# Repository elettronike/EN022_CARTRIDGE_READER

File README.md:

# EN022 CARTRIDGE READER

## Supported Console Cartridge.

## (GB) Game Boy
[Game Boy related schematics](https://github.com/Gekkio/gb-schematics?tab=readme-ov-file) 

[Jeff Frohwein's GameBoy Tech Page](http://www.devrs.com/gb/files/hardware.html)
Cartridge Voltage 3.3V
System Clock: 4MHz

## (GBA) Gameboy Advanced

[retrosix](https://www.retrosix.wiki/schematics-game-boy-advance) Here are the original scanned schematics of the Game Boy Advance console.

## (NES)

[schematics](https://github.com/schenkzoola/NES)
[nesdev cartridge connector](https://www.nesdev.org/wiki/Cartridge_connector)

Cartridge Voltage 3.3V

## (SNES)

### SNES CIC

## (N64) Nintendo 64

## (MS) Master System

## PCE/TG16	

## Wonderswan	

## CASIO  Loopy

## References

# License

All the schematics in this repository are licensed very liberally under CC BY 4.0, so you can copy, distribute, modify, or even sell them commercially if you want. There's just one requirement: attribution

Basically it just means this: don't remove the original creator's name, or at least somehow acknowledge them. [Here's the full description about it in CC BY 4.0(https://creativecommons.org/licenses/by/4.0/#deed-conditions)]

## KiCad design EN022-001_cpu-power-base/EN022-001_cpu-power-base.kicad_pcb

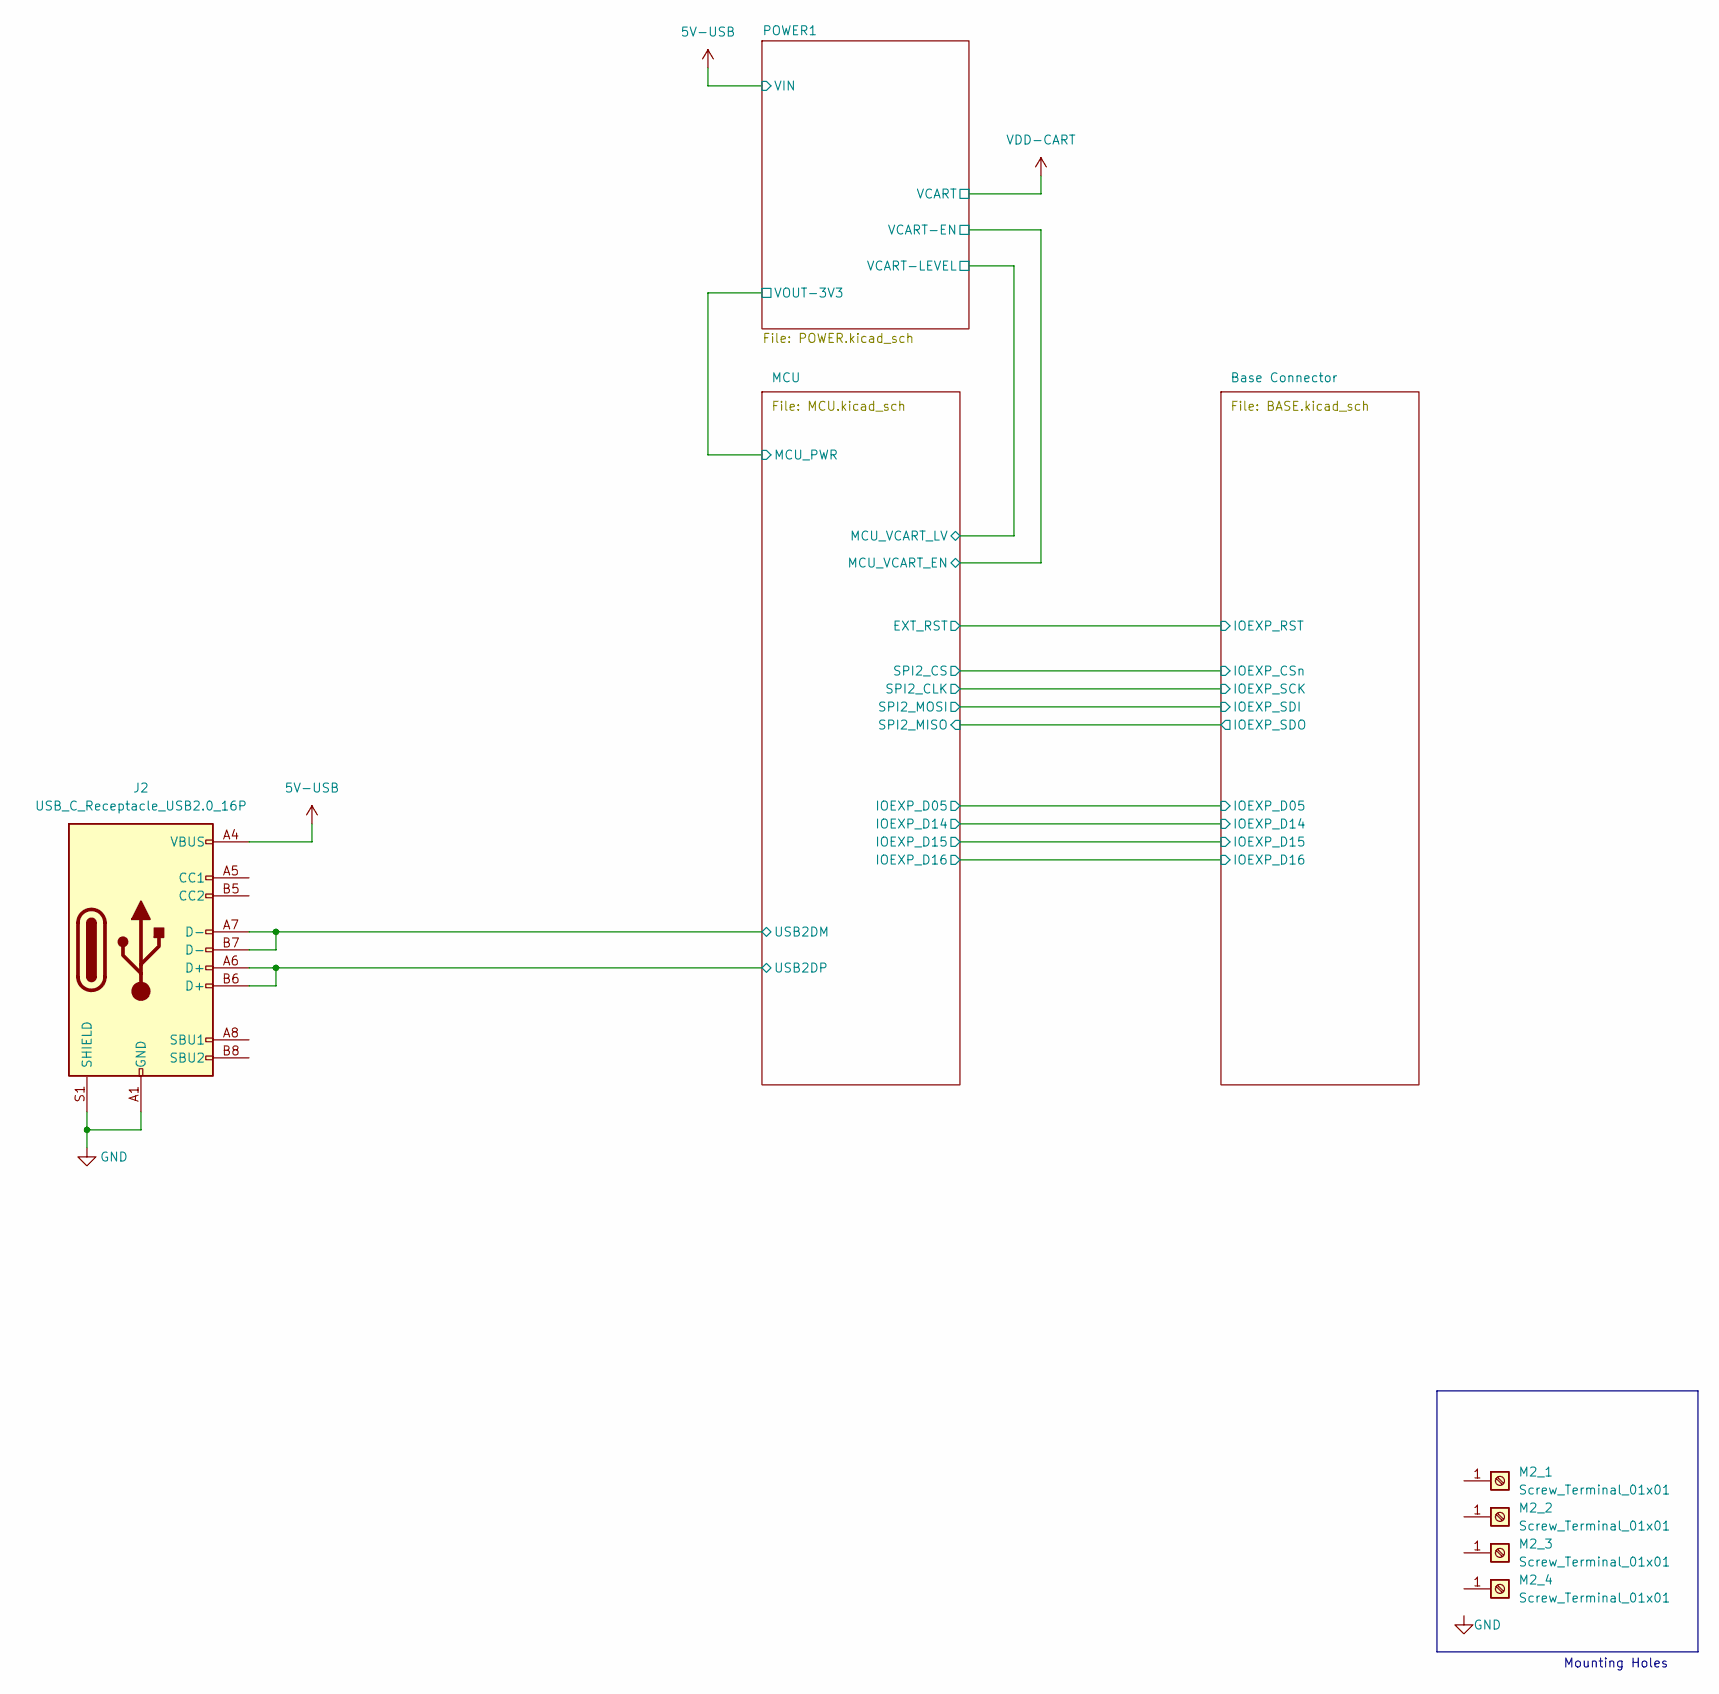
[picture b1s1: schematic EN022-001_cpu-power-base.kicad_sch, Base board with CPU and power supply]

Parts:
J2: USB_C_Receptacle_USB2.0_16P; USB_C_Receptacle_GCT_USB4105-xx-A_16P_TopMnt_Horizontal
M2_1, M2_2, M2_3, M2_4: Screw_Terminal_01x01

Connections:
5V-USB: J2.A4 (VBUS), J2.A9 (VBUS), J2.B4 (VBUS), J2.B9 (VBUS); also elsewhere on the board
/MCU/USB2DM: J2.A7 (D-), J2.B7 (D-); also elsewhere on the board
/MCU/USB2DP: J2.A6 (D+), J2.B6 (D+); also elsewhere on the board
GND: J2.A1 (GND), J2.A12 (GND), J2.B1 (GND), J2.B12 (GND), J2.S1 (SHIELD); also elsewhere on the board

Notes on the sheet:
Mounting Holes

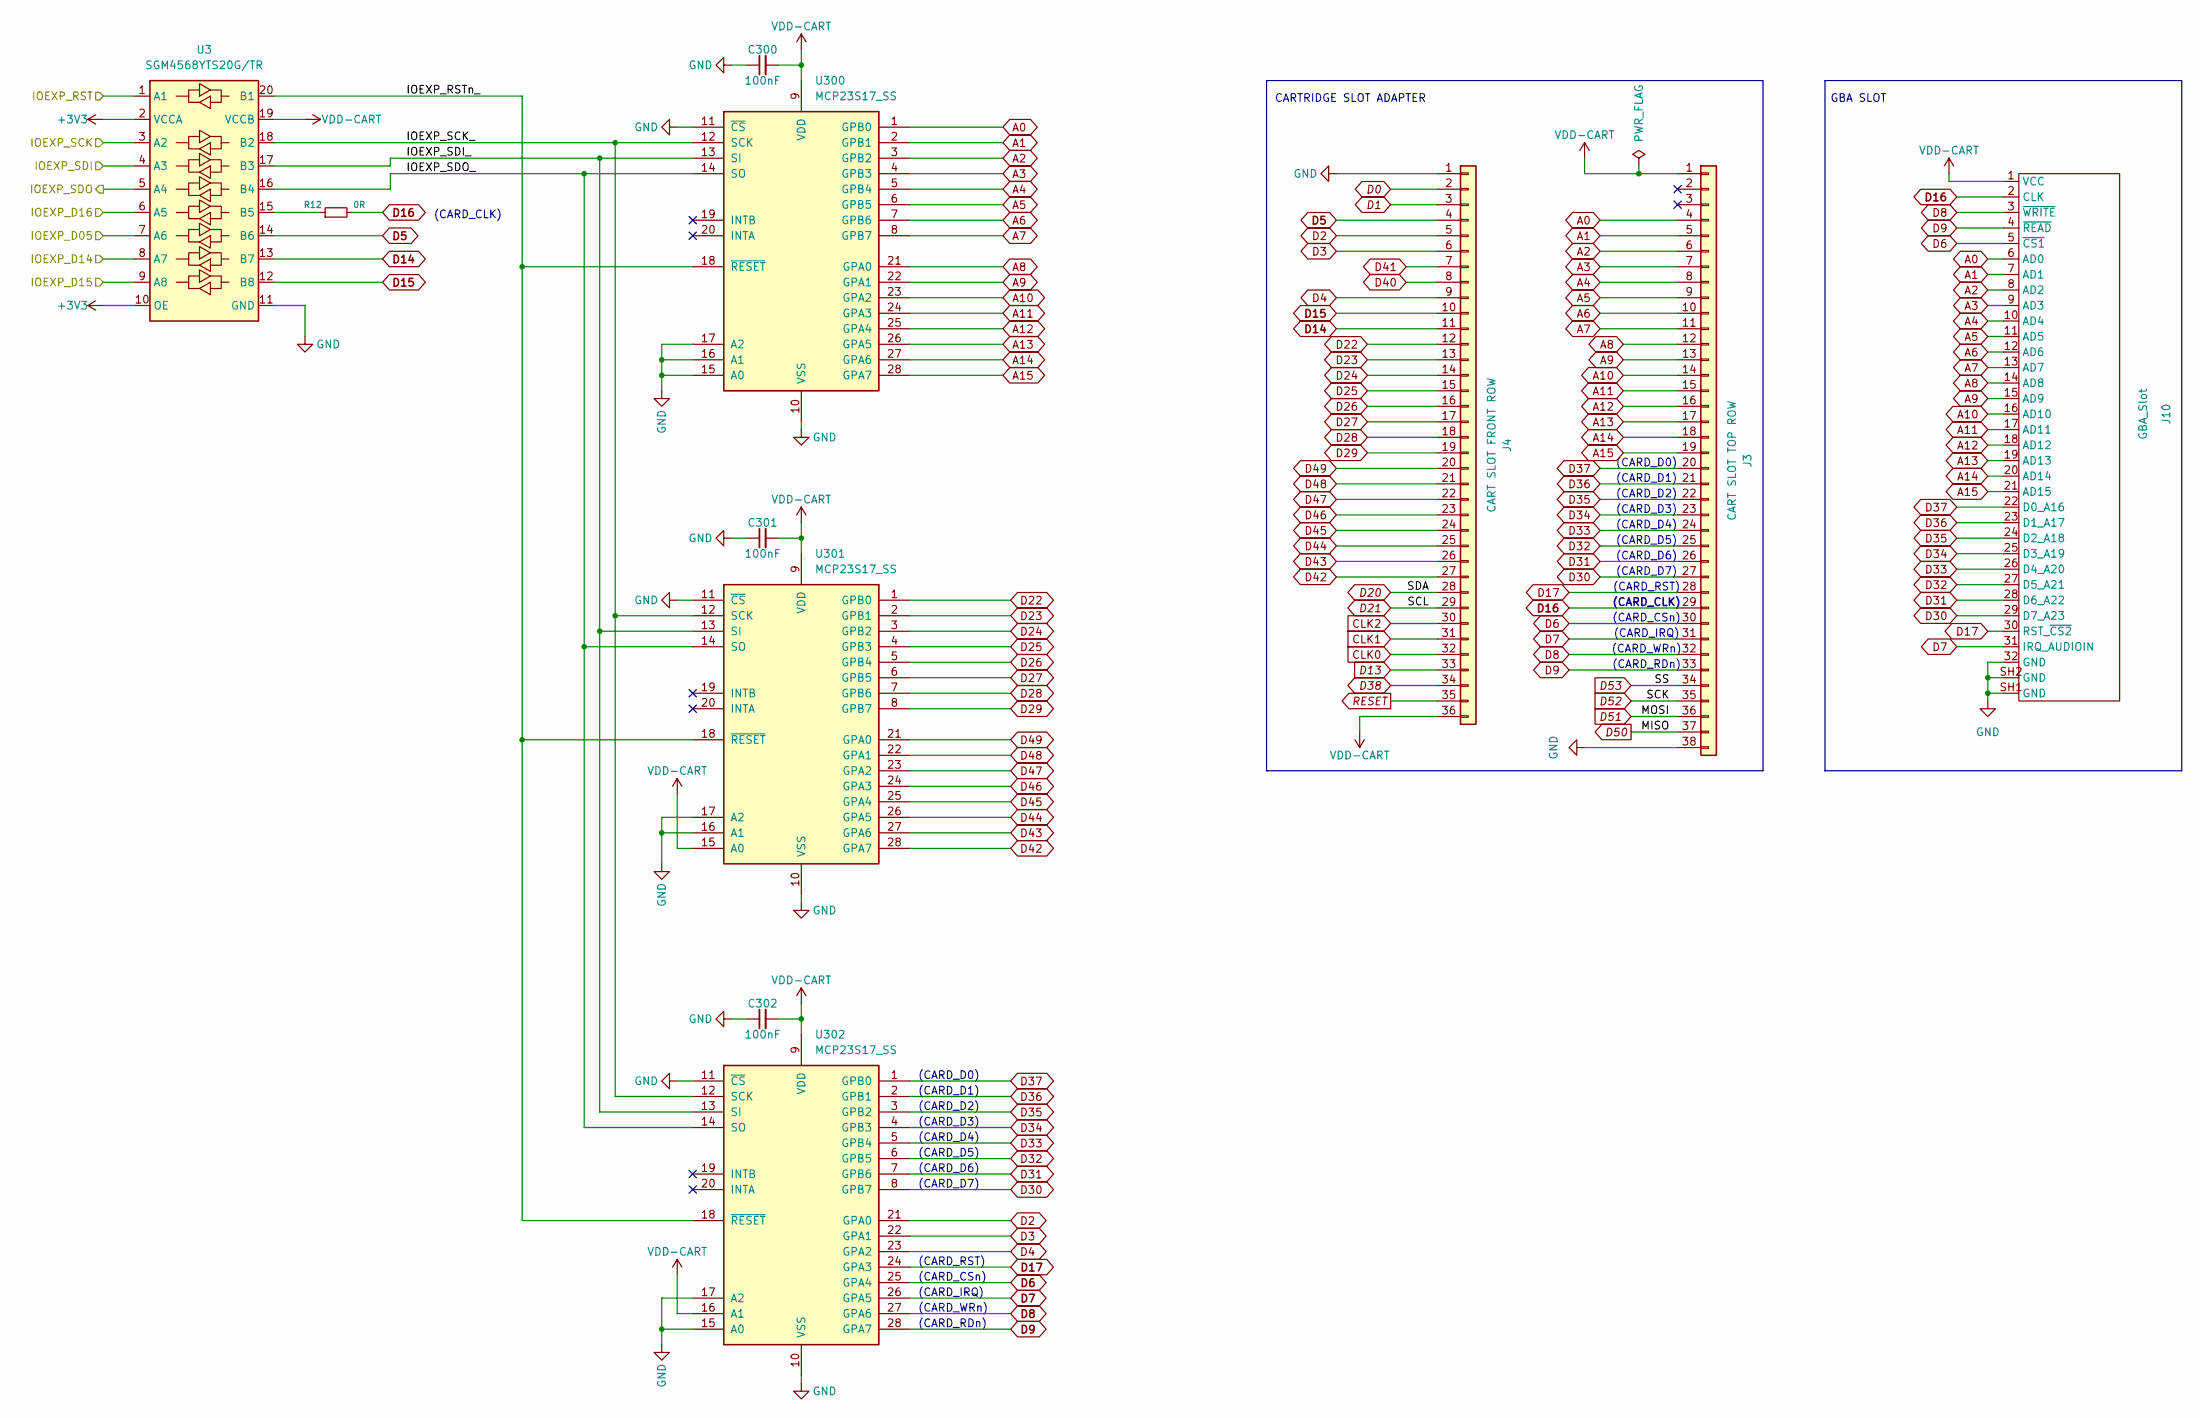
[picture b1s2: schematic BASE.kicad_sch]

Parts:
C300, C301, C302: 100nF; C_0805_2012Metric_Pad1.18x1.45mm_HandSolder
J3: CART SLOT TOP ROW; Cartridge_Port_Adapter-Back
J4: CART SLOT FRONT ROW; Cartridge_Port_Adapter-Front
J10: GBA_Slot
R12: 0R; R_0805_2012Metric_Pad1.20x1.40mm_HandSolder
U3: SGM4568YTS20G/TR; TSSOP-20_4.4x6.5mm_P0.65mm
U300, U301, U302: MCP23S17_SS; SSOP-28_5.3x10.2mm_P0.65mm

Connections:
+3V3: U3.2 (VCCA), U3.10 (OE); also elsewhere on the board
/Base Connector/IOEXP_D05: U3.7 (A6); also elsewhere on the board
/Base Connector/IOEXP_D14: U3.8 (A7); also elsewhere on the board
/Base Connector/IOEXP_D15: U3.9 (A8); also elsewhere on the board
/Base Connector/IOEXP_D16: U3.6 (A5); also elsewhere on the board
/Base Connector/IOEXP_RST: U3.1 (A1); also elsewhere on the board
/Base Connector/IOEXP_RSTn_: U3.20 (B1), U300.18 (~RESET), U301.18 (~RESET), U302.18 (~RESET)
/Base Connector/IOEXP_SCK: U3.3 (A2); also elsewhere on the board
/Base Connector/IOEXP_SCK_: U3.18 (B2), U300.12 (SCK), U301.12 (SCK), U302.12 (SCK)
/Base Connector/IOEXP_SDI: U3.4 (A3); also elsewhere on the board
/Base Connector/IOEXP_SDI_: U3.17 (B3), U300.13 (SI), U301.13 (SI), U302.13 (SI)
/Base Connector/IOEXP_SDO: U3.5 (A4); also elsewhere on the board
/Base Connector/IOEXP_SDO_: U3.16 (B4), U300.14 (SO), U301.14 (SO), U302.14 (SO)
A0: J3.4, J10.6 (AD0), U300.1 (GPB0)
A1: J3.5, J10.7 (AD1), U300.2 (GPB1)
A2: J3.6, J10.8 (AD2), U300.3 (GPB2)
A3: J3.7, J10.9 (AD3), U300.4 (GPB3)
A4: J3.8, J10.10 (AD4), U300.5 (GPB4)
A5: J3.9, J10.11 (AD5), U300.6 (GPB5)
A6: J3.10, J10.12 (AD6), U300.7 (GPB6)
A7: J3.11, J10.13 (AD7), U300.8 (GPB7)
A8: J3.12, J10.14 (AD8), U300.21 (GPA0)
A9: J3.13, J10.15 (AD9), U300.22 (GPA1)
A10: J3.14, J10.16 (AD10), U300.23 (GPA2)
A11: J3.15, J10.17 (AD11), U300.24 (GPA3)
A12: J3.16, J10.18 (AD12), U300.25 (GPA4)
A13: J3.17, J10.19 (AD13), U300.26 (GPA5)
A14: J3.18, J10.20 (AD14), U300.27 (GPA6)
A15: J3.19, J10.21 (AD15), U300.28 (GPA7)
CLK0: J4.32
CLK1: J4.31
CLK2: J4.30
D0: J4.2
D1: J4.3
D2: J4.5, U302.21 (GPA0)
D3: J4.6, U302.22 (GPA1)
D4: J4.9, U302.23 (GPA2)
D5: J4.4, U3.14 (B6)
D6: J3.30, J10.5 (~CS1), U302.25 (GPA4)
D7: J3.31, J10.31 (IRQ_AUDIOIN), U302.26 (GPA5)
D8: J3.32, J10.3 (~WRITE), U302.27 (GPA6)
D9: J3.33, J10.4 (~READ), U302.28 (GPA7)
D13: J4.33
D14: J4.11, U3.13 (B7)
D15: J4.10, U3.12 (B8)
D16: J3.29, J10.2 (CLK), R12.2
D17: J3.28, J10.30 (RST_~CS2), U302.24 (GPA3)
D20: J4.28
D21: J4.29
D22: J4.12, U301.1 (GPB0)
D23: J4.13, U301.2 (GPB1)
D24: J4.14, U301.3 (GPB2)
D25: J4.15, U301.4 (GPB3)
D26: J4.16, U301.5 (GPB4)
D27: J4.17, U301.6 (GPB5)
D28: J4.18, U301.7 (GPB6)
D29: J4.19, U301.8 (GPB7)
D30: J3.27, J10.29 (D7_A23), U302.8 (GPB7)
D31: J3.26, J10.28 (D6_A22), U302.7 (GPB6)
D32: J3.25, J10.27 (D5_A21), U302.6 (GPB5)
D33: J3.24, J10.26 (D4_A20), U302.5 (GPB4)
D34: J3.23, J10.25 (D3_A19), U302.4 (GPB3)
D35: J3.22, J10.24 (D2_A18), U302.3 (GPB2)
D36: J3.21, J10.23 (D1_A17), U302.2 (GPB1)
D37: J3.20, J10.22 (D0_A16), U302.1 (GPB0)
D38: J4.34
D40: J4.8
D41: J4.7
D42: J4.27, U301.28 (GPA7)
D43: J4.26, U301.27 (GPA6)
D44: J4.25, U301.26 (GPA5)
D45: J4.24, U301.25 (GPA4)
D46: J4.23, U301.24 (GPA3)
D47: J4.22, U301.23 (GPA2)
D48: J4.21, U301.22 (GPA1)
D49: J4.20, U301.21 (GPA0)
D50: J3.37
D51: J3.36
D52: J3.35
D53: J3.34
GND: C300.1, C301.1, C302.1, J3.38, J4.1, J10.32 (GND), J10.SH1 (GND), J10.SH2 (GND), U3.11 (GND), U300.10 (VSS), U300.11 (~CS), U300.15 (A0), U300.16 (A1), U300.17 (A2), U301.10 (VSS), U301.11 (~CS), U301.16 (A1), U301.17 (A2), U302.10 (VSS), U302.11 (~CS), U302.15 (A0), U302.17 (A2); also elsewhere on the board
unnamed: R12.1, U3.15 (B5)
RESET: J4.35
VDD-CART: C300.2, C301.2, C302.2, J3.1, J4.36, J10.1 (VCC), U3.19 (VCCB), U300.9 (VDD), U301.9 (VDD), U301.15 (A0), U302.9 (VDD), U302.16 (A1); also elsewhere on the board

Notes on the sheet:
(CARD_D7)
(CARD_D0)
(CARD_CLK)
(CARD_D6)
GBA SLOT
(CARD_D5)
(CARD_D3)
(CARD_WRn)
(CARD_CSn)
(CARD_D1)
CARTRIDGE SLOT ADAPTER
(CARD_D2)
(CARD_IRQ)
(CARD_D4)
(CARD_RDn)
(CARD_RST)

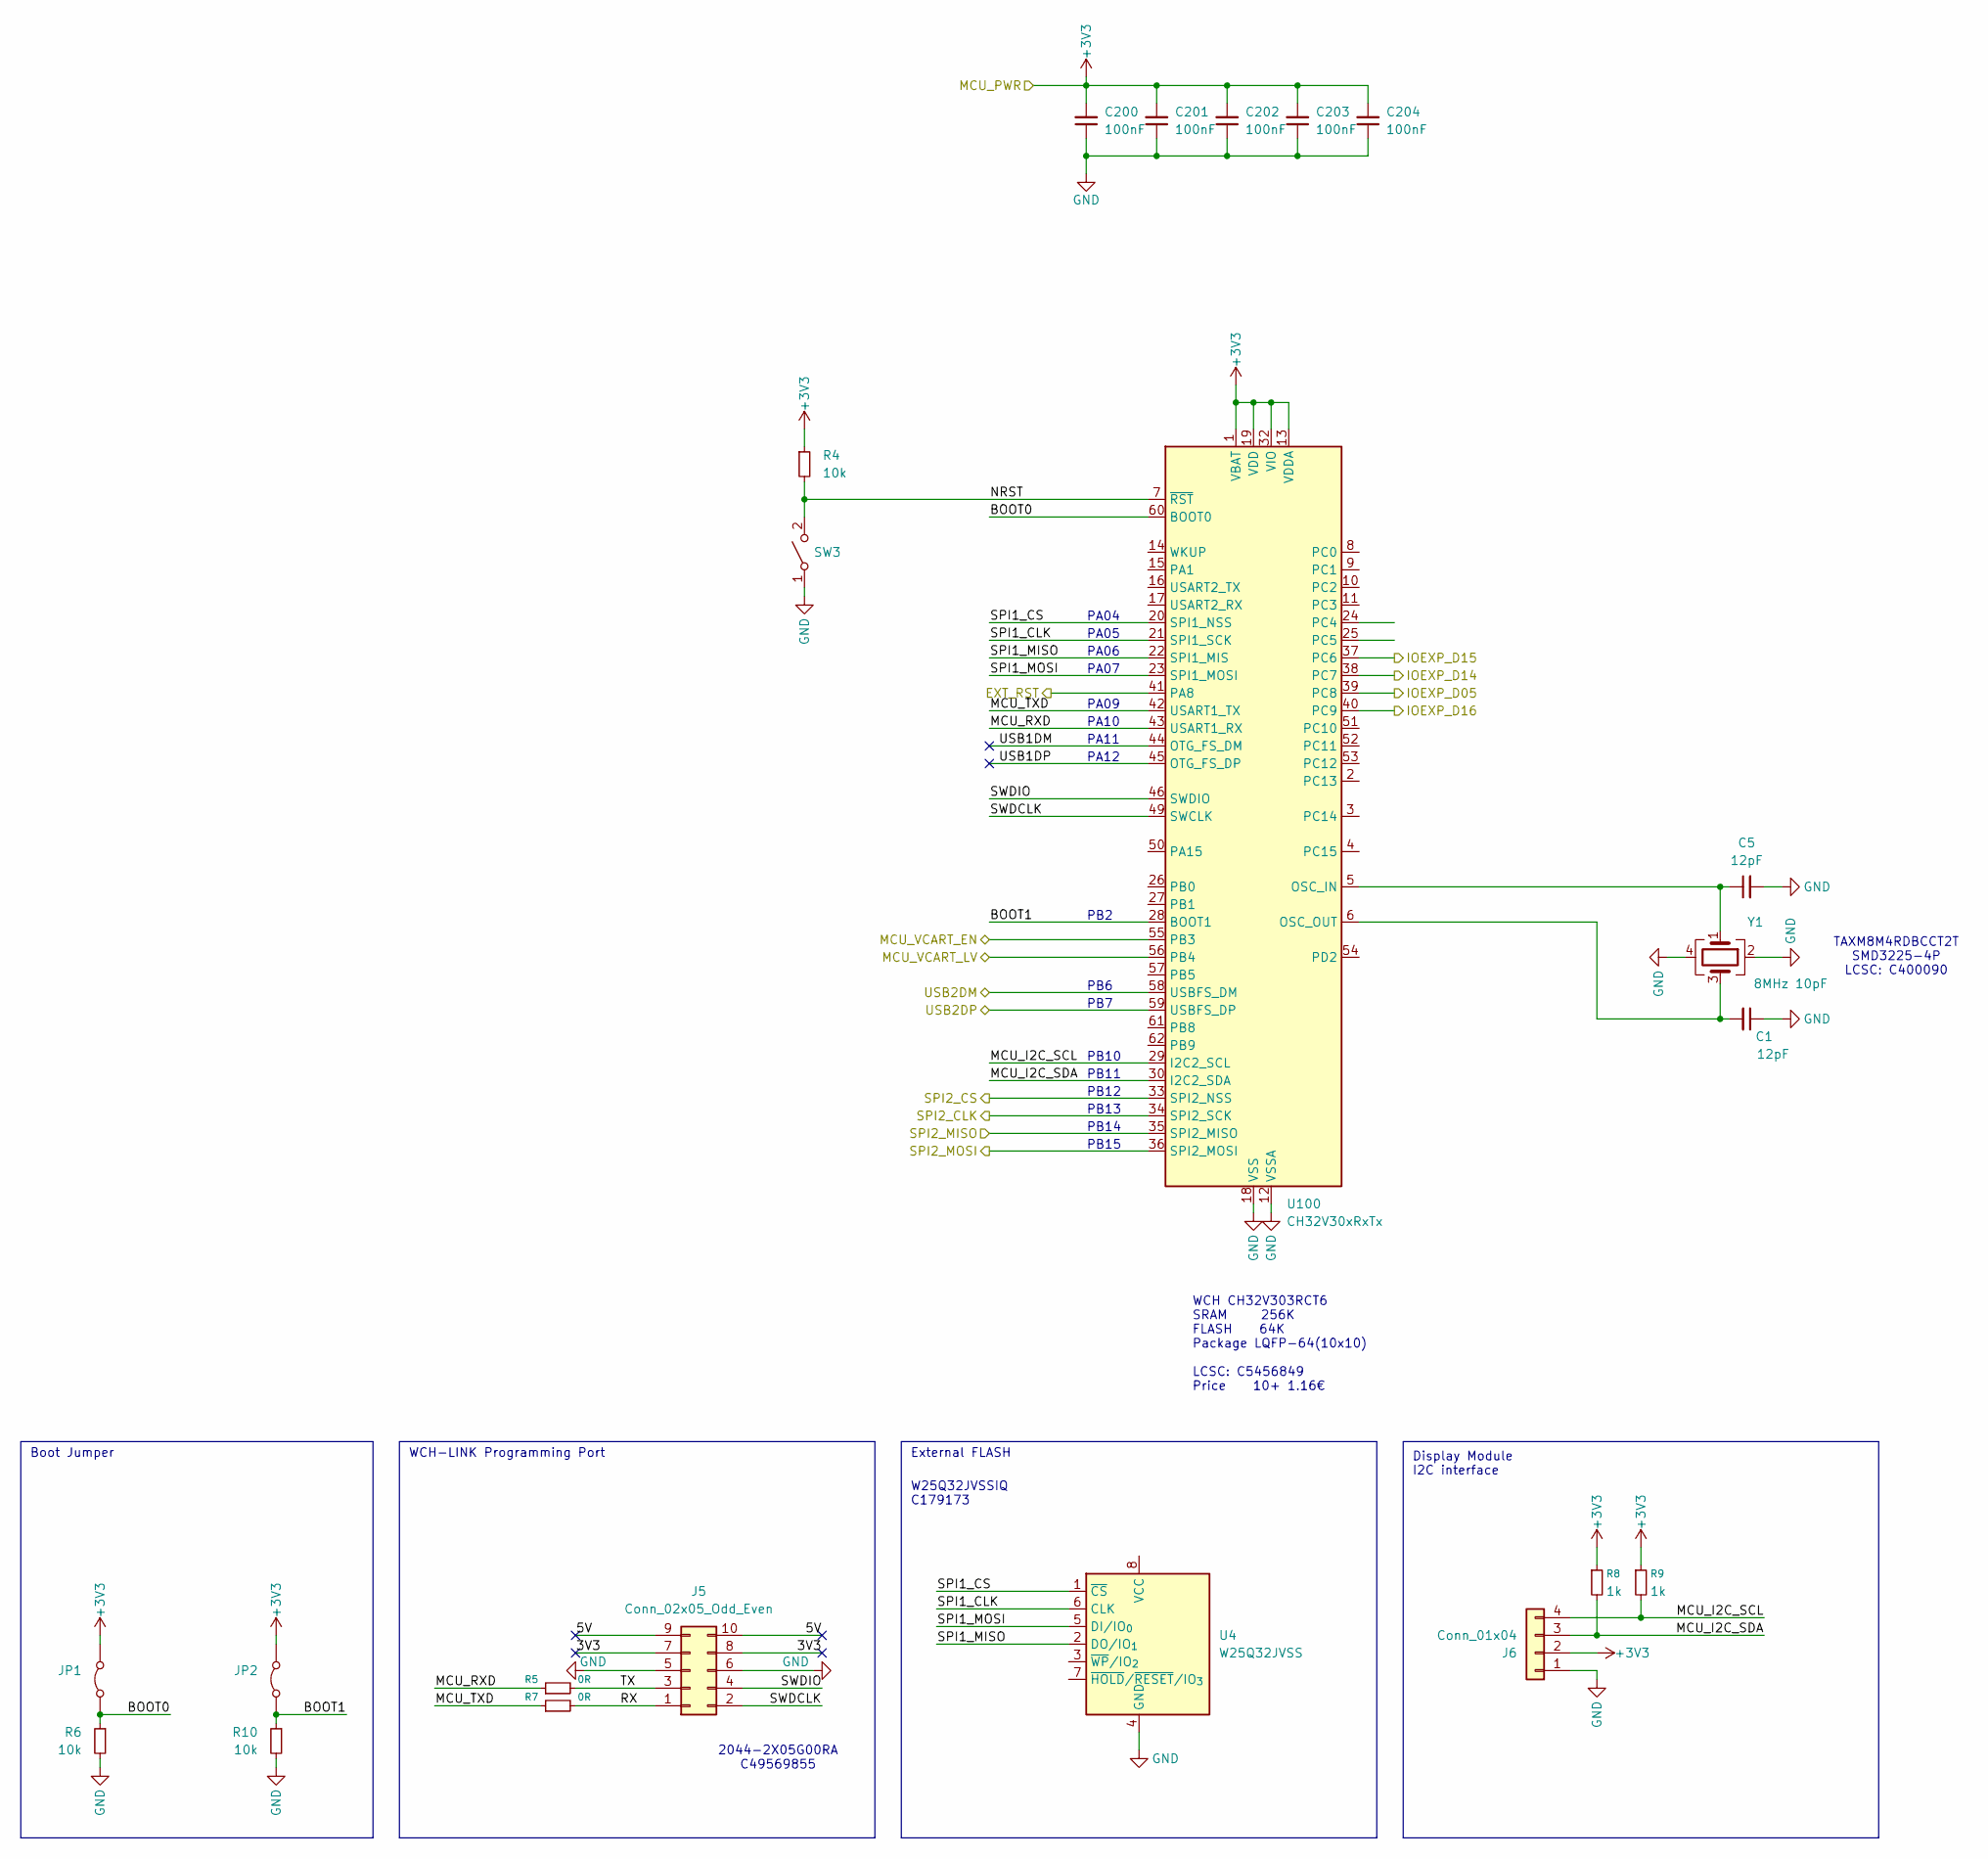
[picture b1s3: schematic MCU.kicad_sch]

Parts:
C1, C5: 12pF; C_0603_1608Metric_Pad1.08x0.95mm_HandSolder
C200, C201, C202, C203, C204: 100nF; C_0805_2012Metric_Pad1.18x1.45mm_HandSolder
J5: Conn_02x05_Odd_Even; PinSocket_2x05_P2.54mm_Horizontal
J6: Conn_01x04; PinHeader_1x04_P2.54mm_Vertical
JP1, JP2: Jumper_2_Bridged; PinHeader_1x02_P2.54mm_Vertical
R4, R6, R10: 10k; R_0805_2012Metric_Pad1.20x1.40mm_HandSolder
R5, R7: 0R; R_0805_2012Metric_Pad1.20x1.40mm_HandSolder
R8, R9: 1k; R_0805_2012Metric_Pad1.20x1.40mm_HandSolder
SW3: TC-6615-7-260G; SW_Tactile_SPST_Angled_PTS645Vx58-2LFS
U4: W25Q32JVSS; SOIC-8_5.3x5.3mm_P1.27mm
U100: CH32V30xRxTx; LQFP-64_10x10mm_P0.5mm
Y1: 8MHz 10pF; Crystal_SMD_3225-4Pin_3.2x2.5mm_HandSoldering

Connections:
+3V3: C200.2, C201.2, C202.2, C203.2, C204.2, J6.2, JP1.1 (A), JP2.1 (A), R4.1, R8.1, R9.1, U100.1 (VBAT), U100.13 (VDDA), U100.19 (VDD), U100.32 (VIO), U100.48 (VDD), U100.64 (VIO); also elsewhere on the board
/Base Connector/IOEXP_D05: U100.39 (PC8); also elsewhere on the board
/Base Connector/IOEXP_D14: U100.38 (PC7); also elsewhere on the board
/Base Connector/IOEXP_D15: U100.37 (PC6); also elsewhere on the board
/Base Connector/IOEXP_D16: U100.40 (PC9); also elsewhere on the board
/Base Connector/IOEXP_RST: U100.41 (PA8); also elsewhere on the board
/Base Connector/IOEXP_SCK: U100.34 (SPI2_SCK); also elsewhere on the board
/Base Connector/IOEXP_SDI: U100.36 (SPI2_MOSI); also elsewhere on the board
/Base Connector/IOEXP_SDO: U100.35 (SPI2_MISO); also elsewhere on the board
/MCU/3V3: J5.7, J5.8
/MCU/5V: J5.9, J5.10
/MCU/BOOT0: JP1.2 (B), R6.1, U100.60 (BOOT0)
/MCU/BOOT1: JP2.2 (B), R10.1, U100.28 (BOOT1)
/MCU/MCU_I2C_SCL: J6.4, R9.2, U100.29 (I2C2_SCL)
/MCU/MCU_I2C_SDA: J6.3, R8.2, U100.30 (I2C2_SDA)
/MCU/MCU_RXD: R5.1, U100.43 (USART1_RX)
/MCU/MCU_TXD: R7.1, U100.42 (USART1_TX)
/MCU/MCU_VCART_EN: U100.55 (PB3); also elsewhere on the board
/MCU/MCU_VCART_LV: U100.56 (PB4); also elsewhere on the board
/MCU/NRST: R4.2, SW3.2 (B), U100.7 (~RST)
/MCU/RX: J5.1, R7.2
/MCU/SPI1_CLK: U4.6 (CLK), U100.21 (SPI1_SCK)
/MCU/SPI1_CS: U4.1 (~CS), U100.20 (SPI1_NSS)
/MCU/SPI1_MISO: U4.2 (DO/IO_{1}), U100.22 (SPI1_MIS)
/MCU/SPI1_MOSI: U4.5 (DI/IO_{0}), U100.23 (SPI1_MOSI)
/MCU/SPI2_CS: U100.33 (SPI2_NSS)
/MCU/SWDCLK: J5.2, U100.49 (SWCLK)
/MCU/SWDIO: J5.4, U100.46 (SWDIO)
/MCU/TX: J5.3, R5.2
/MCU/USB1DM: U100.44 (OTG_FS_DM)
/MCU/USB1DP: U100.45 (OTG_FS_DP)
/MCU/USB2DM: U100.58 (USBFS_DM); also elsewhere on the board
/MCU/USB2DP: U100.59 (USBFS_DP); also elsewhere on the board
GND: C1.1, C5.2, C200.1, C201.1, C202.1, C203.1, C204.1, J5.5, J5.6, J6.1, R6.2, R10.2, SW3.1 (A), U4.4 (GND), U100.12 (VSSA), U100.18 (VSS), U100.31 (VSS), U100.47 (VSS), U100.63 (VSS), Y1.2, Y1.4; also elsewhere on the board
unnamed: C5.1, U100.5 (OSC_IN), Y1.1
unnamed: C1.2, U100.6 (OSC_OUT), Y1.3

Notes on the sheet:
WCH-LINK Programming Port
PB7
WCH CH32V303RCT6 SRAM 256K FLASH 64K Package LQFP-64(10x10) LCSC: C5456849 Price 10+ 1.16€
W25Q32JVSSIQ C179173
PB11
PB15
TAXM8M4RDBCCT2T SMD3225-4P LCSC: C400090
PB2
PB13
PB14
PB12
PB10
External FLASH
Display Module I2C interface
PA10
PB6
PA04
PA11
PA05
Boot Jumper
PA09
PA06
2044-2X05G00RA C49569855
PA12
PA07

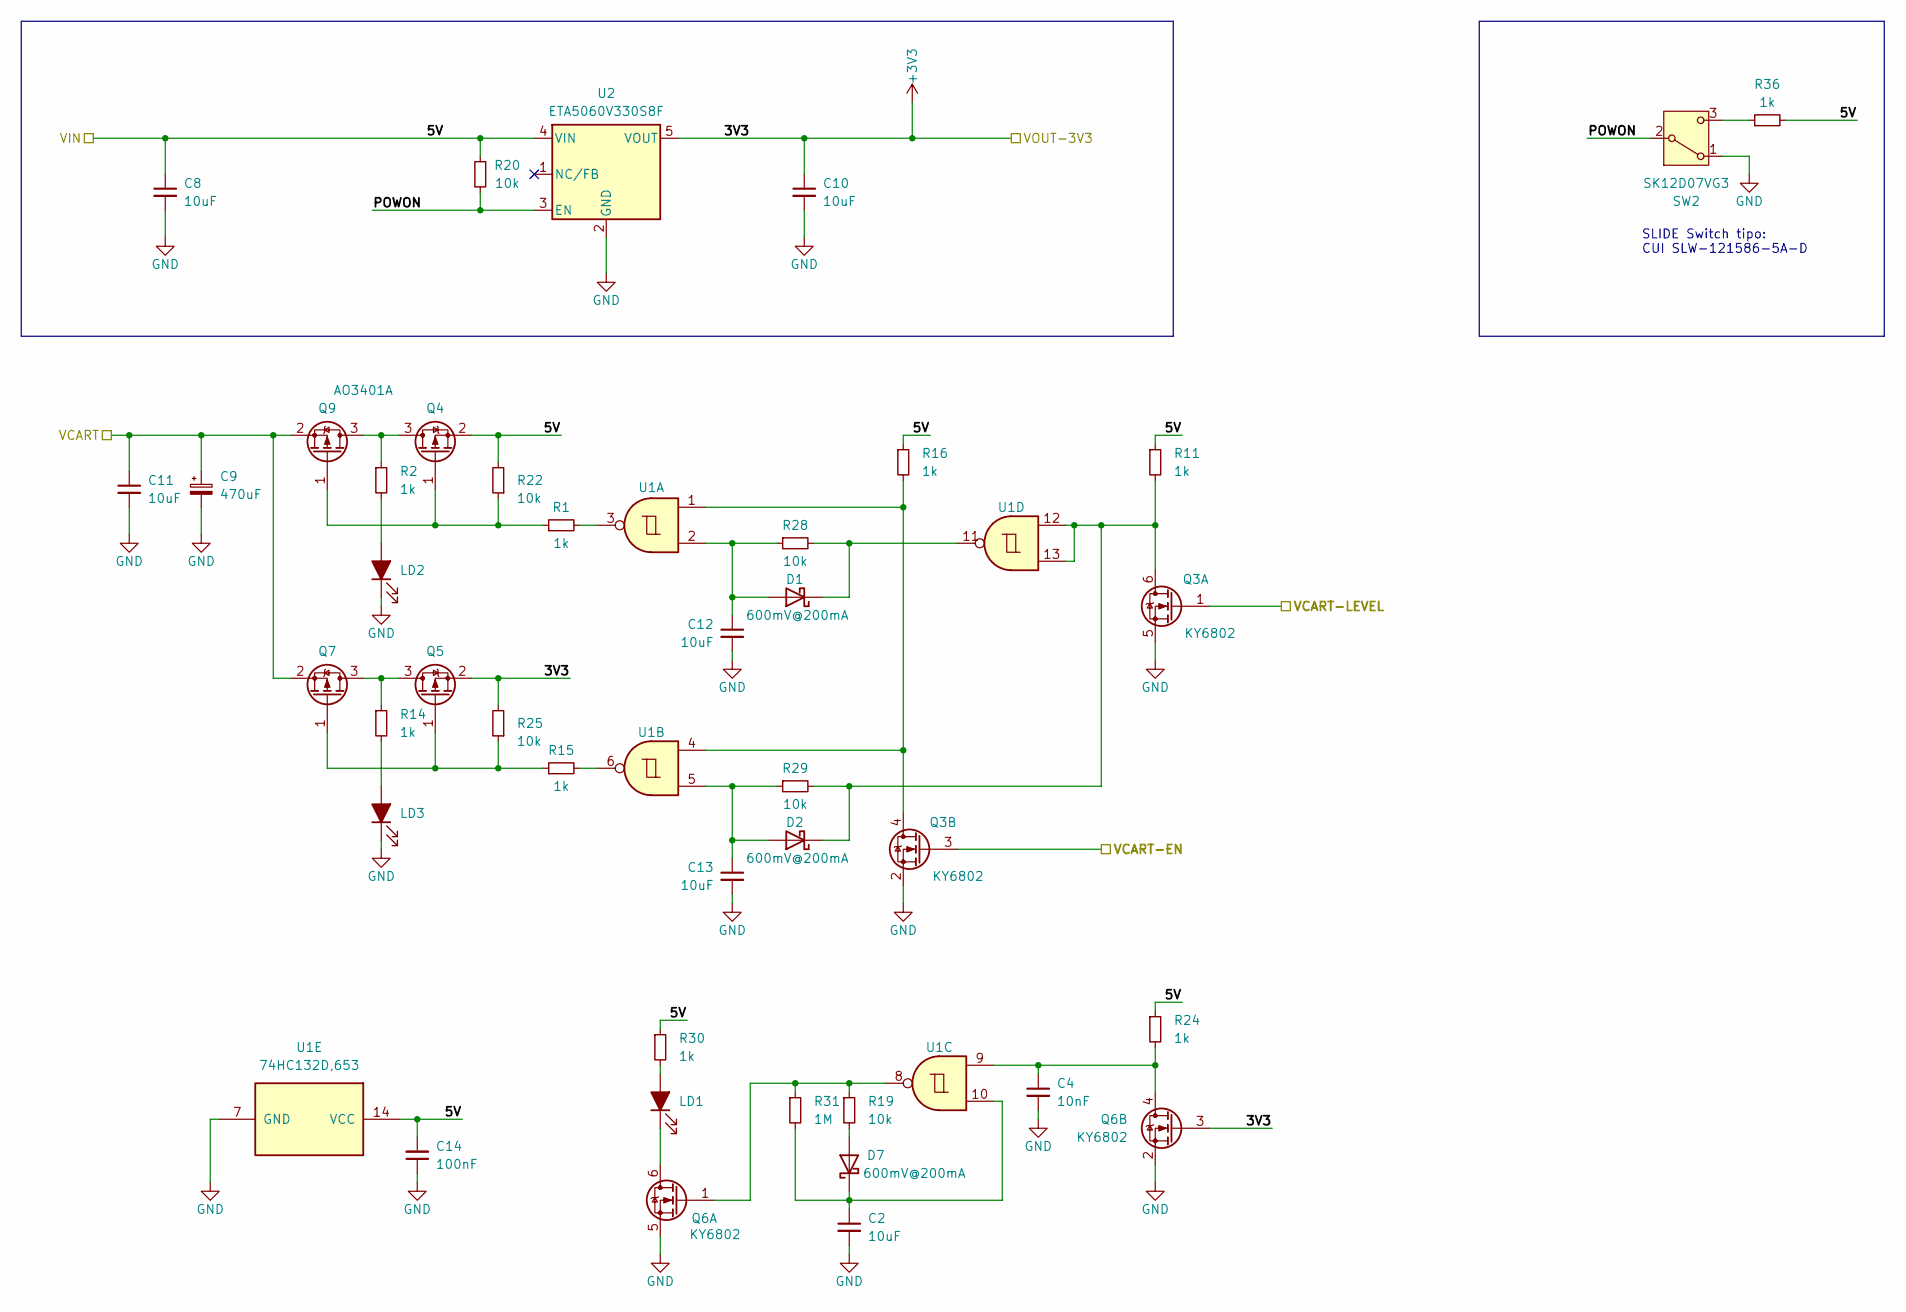
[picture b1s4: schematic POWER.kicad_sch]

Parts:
C2, C8, C10, C11, C12, C13: 10uF; C_1206_3216Metric_Pad1.33x1.80mm_HandSolder
C4: 10nF; C_0805_2012Metric_Pad1.18x1.45mm_HandSolder
C9: 470uF; CP_Elec_6.3x7.7
C14: 100nF; C_0805_2012Metric_Pad1.18x1.45mm_HandSolder
D1, D2, D7: 600mV@200mA; D_SOD-123F
LD1, LD2, LD3: LED_Filled; LED_0805_2012Metric_Pad1.15x1.40mm_HandSolder
Q3, Q6: KY6802; SOT-23-6_Handsoldering
Q4, Q5, Q7, Q9: AO3401; SOT-23
R1, R2, R11, R14, R15, R16, R24, R30, R36: 1k; R_0805_2012Metric_Pad1.20x1.40mm_HandSolder
R19, R20, R22, R25, R28, R29: 10k; R_0805_2012Metric_Pad1.20x1.40mm_HandSolder
R31: 1M; R_0805_2012Metric_Pad1.20x1.40mm_HandSolder
SW2: SK12D07VG3; SW_Slide_SPDT_Angled_CK_OS102011MA1Q
U1: 74HC132D,653; SOIC-14_3.9x8.7mm_P1.27mm
U2: ETA5060V330S8F; SOT-89-5

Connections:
5V-USB: C8.1, C14.2, Q4.2 (S), R11.1, R16.1, R20.1, R22.2, R24.1, R30.1, R36.2, U1.14 (VCC), U2.4 (VIN); also elsewhere on the board
+3V3: C10.1, Q5.2 (S), Q6.3 (G), R25.2, U2.5 (VOUT); also elsewhere on the board
/MCU/MCU_VCART_EN: Q3.3 (G); also elsewhere on the board
/MCU/MCU_VCART_LV: Q3.1 (G); also elsewhere on the board
/POWER1/POWON: R20.2, SW2.2 (B), U2.3 (EN)
GND: C2.2, C4.2, C8.2, C9.2, C10.2, C11.2, C12.2, C13.2, C14.1, LD2.1 (K), LD3.1 (K), Q3.2 (S), Q3.5 (S), Q6.2 (S), Q6.5 (S), SW2.1 (A), U1.7 (GND), U2.2 (GND); also elsewhere on the board
unnamed: C12.1, D1.2 (A), R28.1, U1.2
unnamed: D1.1 (K), R28.2, U1.11
unnamed: C13.1, D2.2 (A), R29.1, U1.5
unnamed: D2.1 (K), Q3.6 (D), R11.2, R29.2, U1.12, U1.13
unnamed: D7.2 (A), R19.2
unnamed: C2.1, D7.1 (K), R31.2, U1.10
unnamed: LD1.2 (A), R30.2
unnamed: LD1.1 (K), Q6.6 (D)
unnamed: LD2.2 (A), R2.2
unnamed: LD3.2 (A), R14.2
unnamed: Q3.4 (D), R16.2, U1.1, U1.4
unnamed: Q4.3 (D), Q9.3 (D), R2.1
unnamed: Q4.1 (G), Q9.1 (G), R1.1, R22.1
unnamed: Q5.3 (D), Q7.3 (D), R14.1
unnamed: Q5.1 (G), Q7.1 (G), R15.1, R25.1
unnamed: Q6.1 (G), R19.1, R31.1, U1.8
unnamed: C4.1, Q6.4 (D), R24.2, U1.9
unnamed: R1.2, U1.3
unnamed: R15.2, U1.6
unnamed: R36.1, SW2.3 (C)
VDD-CART: C9.1, C11.1, Q7.2 (S), Q9.2 (S); also elsewhere on the board

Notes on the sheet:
SLIDE Switch tipo: CUI SLW-121586-5A-D

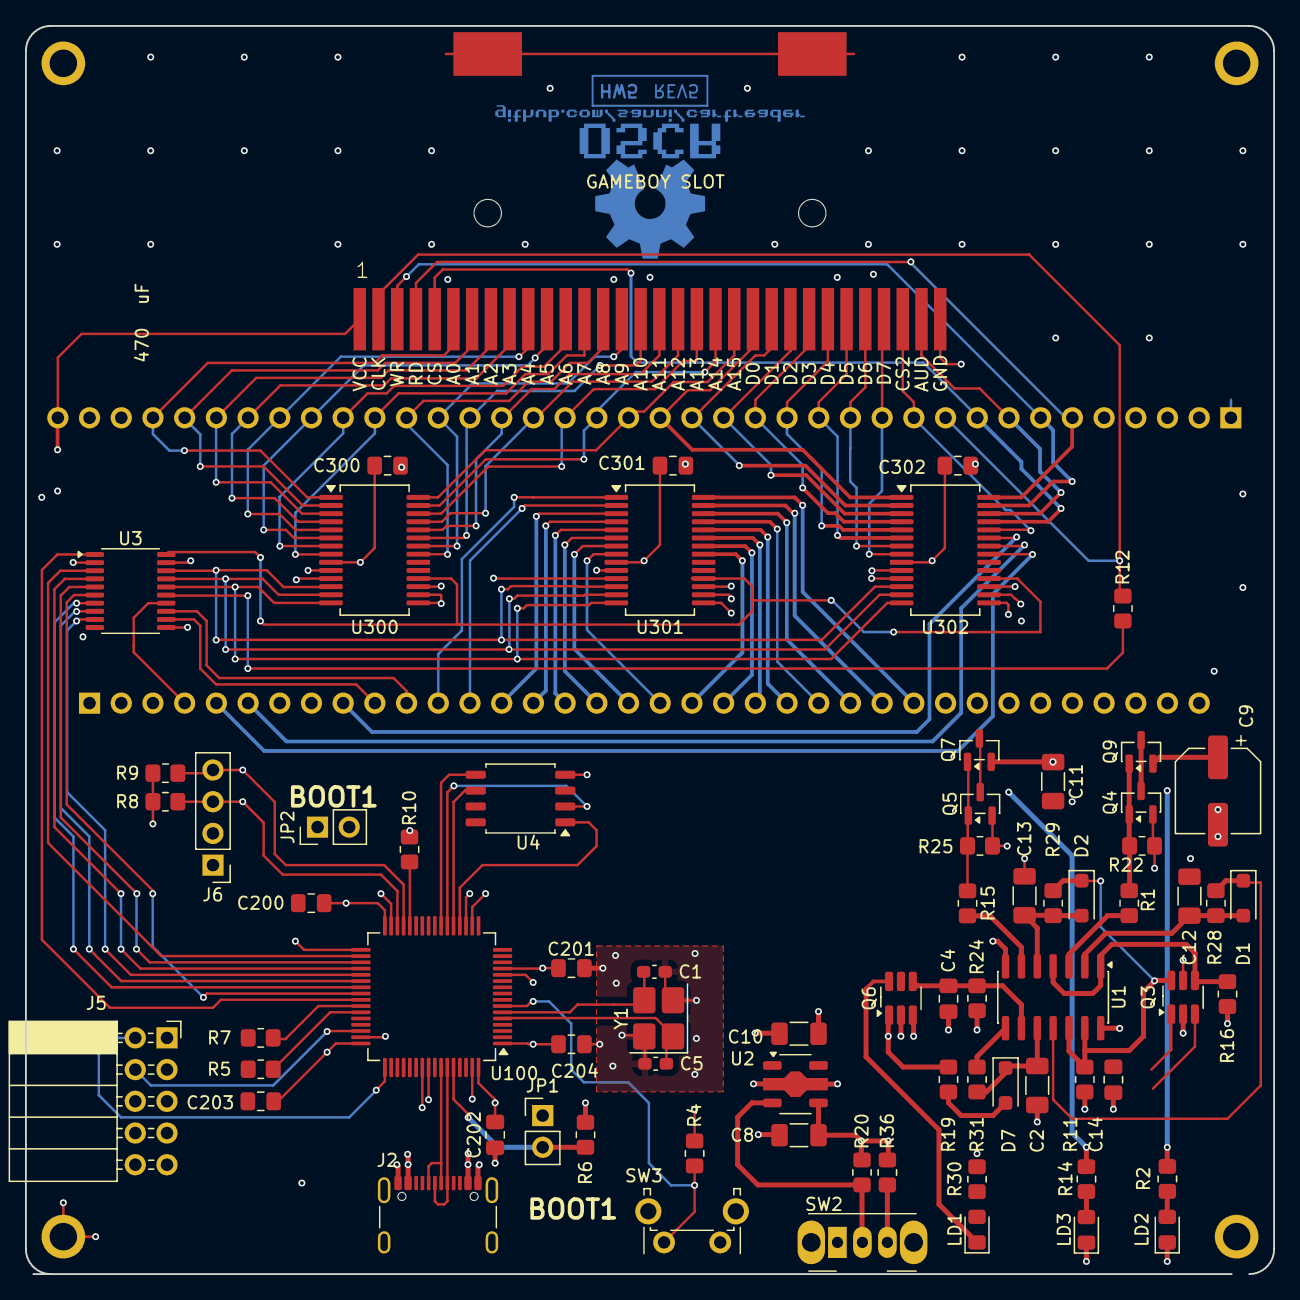
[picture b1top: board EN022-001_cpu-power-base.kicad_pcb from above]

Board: 4 copper layers, 100.0 x 100.0 mm, 78 parts (0 on the bottom side), 113 nets.
